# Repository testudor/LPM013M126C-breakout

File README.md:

# LPM013M126C breakout

This is a breakout board for the LPM013M126C MIP display from JDI. It makes it easy to use with various dev boards like Arduino, etc.

## Wiring

> **Note** Logic levels as well as supply voltages are 3.3 V. If your use case requires 5 V you'll have to use a level shifter and change the current limiting resistors for the backlight LEDs.

> **Note** Yes, this board has many pins. The display offers the possibility to use separate analog/logic power supplies and I decided to keep this functionality. Same goes for the backlight. For most use cases it's possible to use a common supply for everything.

| PIN      | Description                        | Connect to                     |
| -------- | ---------------------------------- | ------------------------------ |
| SCLK     | Serial Clock Signal                | Connect to MCU SPI Clock       |
| SI       | Serial Data Input Signal           | Connect to MCU SPI MOSI        |
| SCS      | Chip Select Signal                 | Connect to MCU SPI Chip Select |
| EXTCOMIN | COM Inversion Polarity Input       | Not connected                  |
| DISP     | Display ON/OFF Switching Signal    | Connect to any digital pin     |
| VDDA     | Power Supply for Analog            | Connect to +3.3 V              |
| VDD      | Power Supply for Logic             | Connect to +3.3 V              |
| VDDL     | Power Supply for LED               | Connect to +3.3 V              |
| EXTMODE  | COM Inversion Mode Select Terminal | Not connected                  |
| VSS      | Logic Ground                       | Connect to GND                 |
| VSSA     | Analog Ground                      | Connect to GND                 |
| VSSL     | LED Ground                         | Connect to GND                 |
| BL       | LED Backlight Input                | Connect to any digital pin     |

## EXTMODE Jumper

Set EXTMODE to 'L' for use with the library mentioned below

## Software

The display works great with the [JDI_MIP_Display](https://github.com/Gbertaz/JDI_MIP_Display) library! Just make sure to set the right resolution in the config file.

## Further Information

For more information regarding the display please refer to the [official datasheet](https://www.j-display.com/product/pdf/Datasheet/5LPM013M126C_specification_ver03.pdf)!

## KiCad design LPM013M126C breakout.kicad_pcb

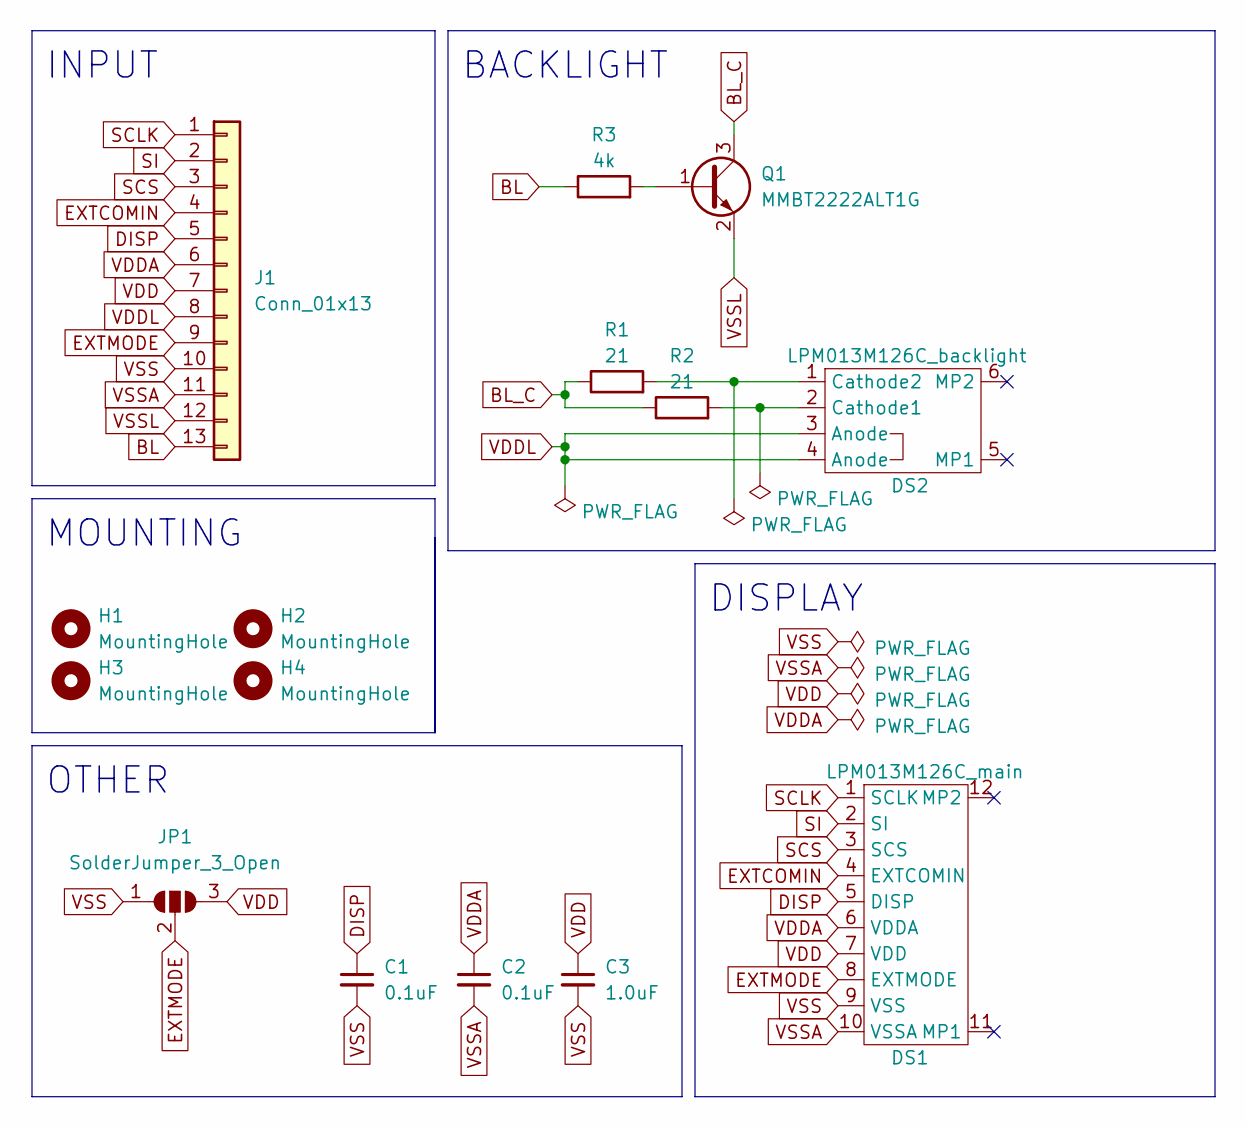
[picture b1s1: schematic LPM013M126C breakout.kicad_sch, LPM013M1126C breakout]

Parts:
C1, C2: 0.1uF; C_0402_1005Metric
C3: 1.0uF; C_0402_1005Metric
DS1: LPM013M126C_main; 5034801000
DS2: LPM013M126C_backlight; 503480-0400
H1, H2, H3, H4: MountingHole; MountingHole_3.2mm_M3_ISO14580_Pad_TopBottom
J1: Conn_01x13; PinHeader_1x13_P2.54mm_Vertical
JP1: SolderJumper_3_Open; SolderJumper-3_P1.3mm_Open_RoundedPad1.0x1.5mm_NumberLabels
Q1: MMBT2222ALT1G; SOT-23
R1, R2: 21; R_0402_1005Metric
R3: 4k; R_0402_1005Metric

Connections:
BL: J1.13, R3.1
BL_C: Q1.3 (C), R1.1, R2.1
DISP: C1.1, DS1.5 (DISP), J1.5
EXTCOMIN: DS1.4 (EXTCOMIN), J1.4
EXTMODE: DS1.8 (EXTMODE), J1.9, JP1.2 (C)
unnamed: DS2.1 (Cathode2), R1.2
unnamed: DS2.2 (Cathode1), R2.2
unnamed: Q1.1 (B), R3.2
SCLK: DS1.1 (SCLK), J1.1
SCS: DS1.3 (SCS), J1.3
SI: DS1.2 (SI), J1.2
VDD: C3.1, DS1.7 (VDD), J1.7, JP1.3 (B)
VDDA: C2.1, DS1.6 (VDDA), J1.6
VDDL: DS2.3 (Anode), DS2.4 (Anode), J1.8
VSS: C1.2, C3.2, DS1.9 (VSS), J1.10, JP1.1 (A)
VSSA: C2.2, DS1.10 (VSSA), J1.11
VSSL: J1.12, Q1.2 (E)

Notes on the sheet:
DISPLAY
MOUNTING
OTHER
INPUT
BACKLIGHT

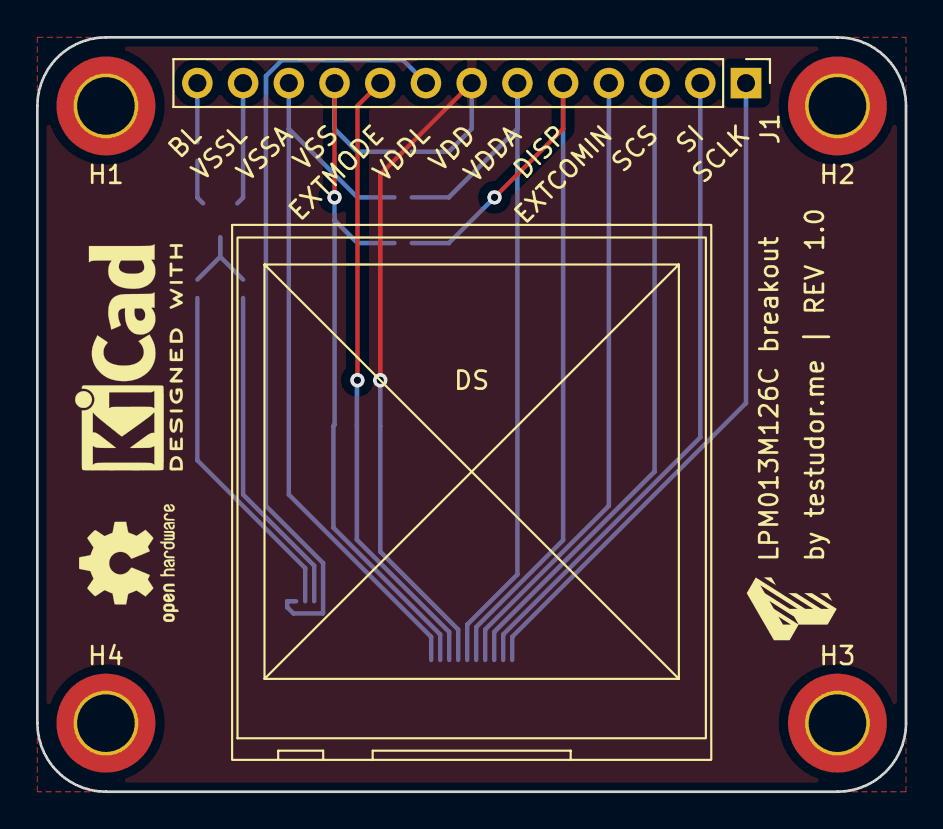
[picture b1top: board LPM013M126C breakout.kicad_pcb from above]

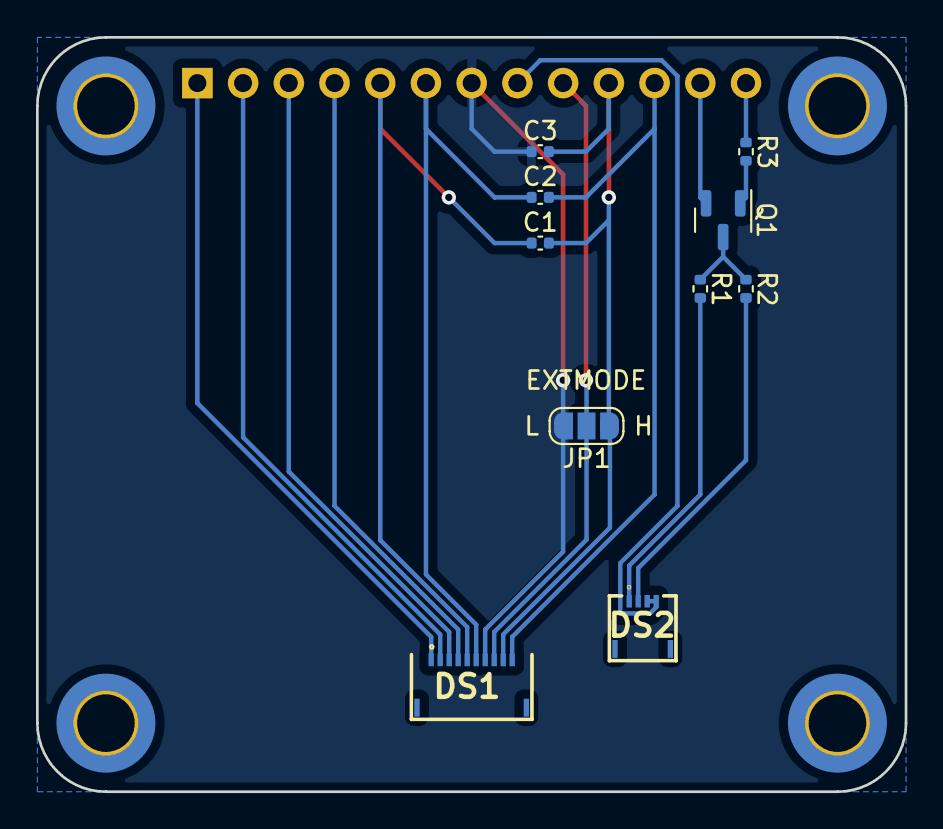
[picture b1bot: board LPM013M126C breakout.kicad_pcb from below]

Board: 2 copper layers, 48.3 x 41.9 mm, 19 parts (10 on the bottom side), 17 nets.

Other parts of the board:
DS: LPM013M126C; LPM013M126C_silk
LOGO1: KiCad-Logo2_5mm_SilkScreen
LOGO2: OSHW-Logo2_7.3x6mm_SilkScreen
LOGO3: Testudor-Logo_5mm_SilkScreen

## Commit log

2022-08-03 add license
2022-08-03 change logo to library version
2022-08-03 initial github actions test
2022-08-03 initial github actions test (#1)
2022-08-03 rename actions
2022-08-03 fix references for R1, R2
2022-08-04 initial preliminary readme
2022-08-04 change readme wording
2022-08-04 Add BJT for backlight
2022-08-04 add updated wiring table to readme
2022-08-04 add reference designators to logos
2022-08-04 fix typo on PCB silkscreen
2022-09-07 modified pipeline to only run DRC and ERC checks
2022-09-07 fix workflow badge path
2022-09-09 added photo to README
2022-09-09 changed README pic to better demonstrate color capability of the display
